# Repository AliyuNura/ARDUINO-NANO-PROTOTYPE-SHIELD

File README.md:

# ARDUINO-NANO-PROTOTYPE-SHIELD
This is an Arduino nano prototype shield designed using kicad.It has a 12v power supply jack,and have +5v and +3.3v pins.I will try to add more features like bluetooth and wifi to it.

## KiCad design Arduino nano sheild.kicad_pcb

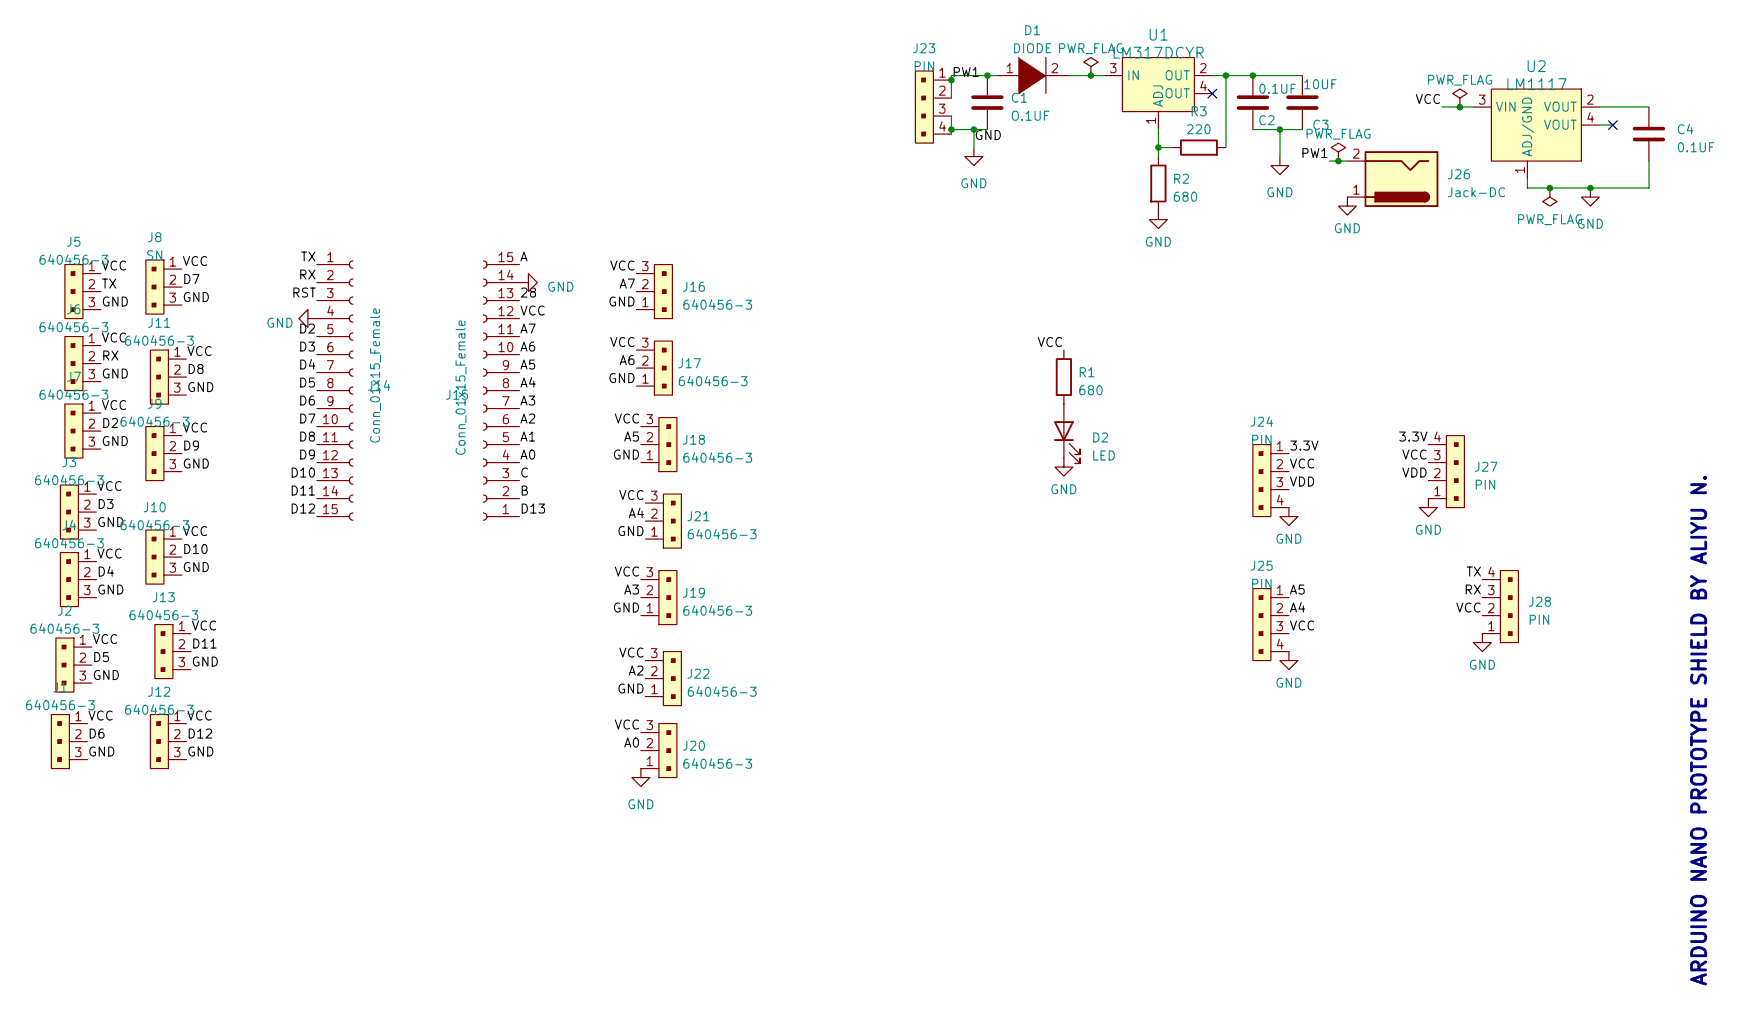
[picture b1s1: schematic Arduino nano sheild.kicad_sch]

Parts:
C1: O.1UF; C_0603_1608Metric_Pad1.08x0.95mm_HandSolder
C2, C4: 0.1UF; C_0603_1608Metric_Pad1.08x0.95mm_HandSolder
C3: 10UF; C_0603_1608Metric_Pad1.08x0.95mm_HandSolder
D1: DIODE; D_0603_1608Metric_Pad1.05x0.95mm_HandSolder
D2: LED; LED_D3.0mm
J1, J2, J3, J4, J5, J6, J7, J9, J10, J11, J12, J13, J16, J17, J18, J19, J20, J21, J22: 640456-3; FanPinHeader_1x03_P2.54mm_Vertical; MPN 640456-3; Digi-Key_PN A19470-ND
J8: SN; FanPinHeader_1x03_P2.54mm_Vertical; MPN 640456-3; Digi-Key_PN A19470-ND
J14, J15: Conn_01x15_Female; PinHeader_1x15_P2.54mm_Vertical
J23, J24, J25, J27, J28: PIN; PinHeader_1x4_P2.5mm_Drill1.1mm; MPN B4B-XH-A(LF)(SN); Digi-Key_PN 455-2249-ND
J26: Jack-DC; BarrelJack_GCT_DCJ200-10-A_Horizontal
R1, R2: 680; R_0603_1608Metric_Pad0.98x0.95mm_HandSolder
R3: 220; R_0603_1608Metric_Pad0.98x0.95mm_HandSolder
U1: LM317DCYR; SOT-223-4; MPN LM317DCYR; Digi-Key_PN 296-12602-1-ND
U2: LM1117; SOT-223; MPN LM1117MPX-3.3/NOPB; Digi-Key_PN LM1117MPX-3.3/NOPBCT-ND

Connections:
/3.3V: J24.1, J27.4
/28: J15.13
/A: J15.15
/A0: J15.4, J20.2
/A1: J15.5
/A2: J15.6, J22.2
/A3: J15.7, J19.2
/A4: J15.8, J21.2, J25.2
/A5: J15.9, J18.2, J25.1
/A6: J15.10, J17.2
/A7: J15.11, J16.2
/B: J15.2
/C: J15.3
/D2: J7.2, J14.5
/D3: J3.2, J14.6
/D4: J4.2, J14.7
/D5: J2.2, J14.8
/D6: J1.2, J14.9
/D7: J8.2, J14.10
/D8: J11.2, J14.11
/D9: J9.2, J14.12
/D10: J10.2, J14.13
/D11: J13.2, J14.14
/D12: J12.2, J14.15
/D13: J15.1
/PW1: C1.1, D1.1 (K), J23.1, J23.2, J26.2
/RST: J14.3
/RX: J6.2, J14.2, J28.3
/TX: J5.2, J14.1, J28.4
/VCC: J1.1, J2.1, J3.1, J4.1, J5.1, J6.1, J7.1, J8.1, J9.1, J10.1, J11.1, J12.1, J13.1, J15.12, J16.3, J17.3, J18.3, J19.3, J20.3, J21.3, J22.3, J24.2, J25.3, J27.3, J28.2, R1.1, U2.3 (VIN)
/VDD: J24.3, J27.2
GND: C1.2, C2.2, C3.2, C4.2, D2.1 (K), J1.3, J2.3, J3.3, J4.3, J5.3, J6.3, J7.3, J8.3, J9.3, J10.3, J11.3, J12.3, J13.3, J14.4, J15.14, J16.1, J17.1, J18.1, J19.1, J20.1, J21.1, J22.1, J23.3, J23.4, J24.4, J25.4, J26.1, J27.1, J28.1, R2.2, U2.1 (ADJ/GND)
unnamed: D1.2 (A), U1.3 (IN)
unnamed: D2.2 (A), R1.2
unnamed: R2.1, R3.1, U1.1 (ADJ)
unnamed: C2.1, C3.1, R3.2, U1.2 (OUT)
unnamed: C4.1, U2.2 (VOUT)

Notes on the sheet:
ARDUINO NANO PROTOTYPE SHIELD BY ALIYU N.

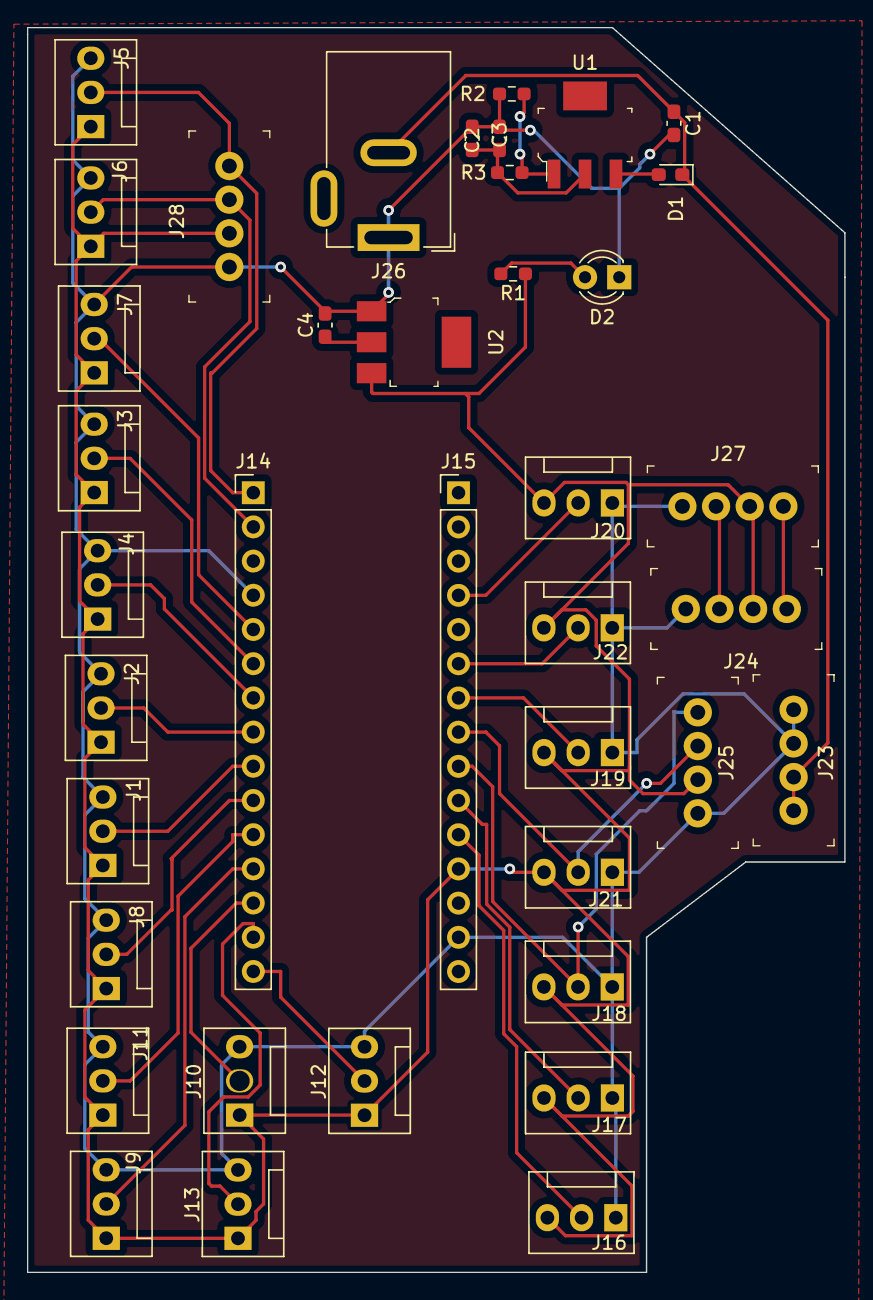
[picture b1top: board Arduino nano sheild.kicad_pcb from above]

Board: 2 copper layers, 60.7 x 92.5 mm, 39 parts (0 on the bottom side), 30 nets.

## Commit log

2022-09-14 arduino nano shield
